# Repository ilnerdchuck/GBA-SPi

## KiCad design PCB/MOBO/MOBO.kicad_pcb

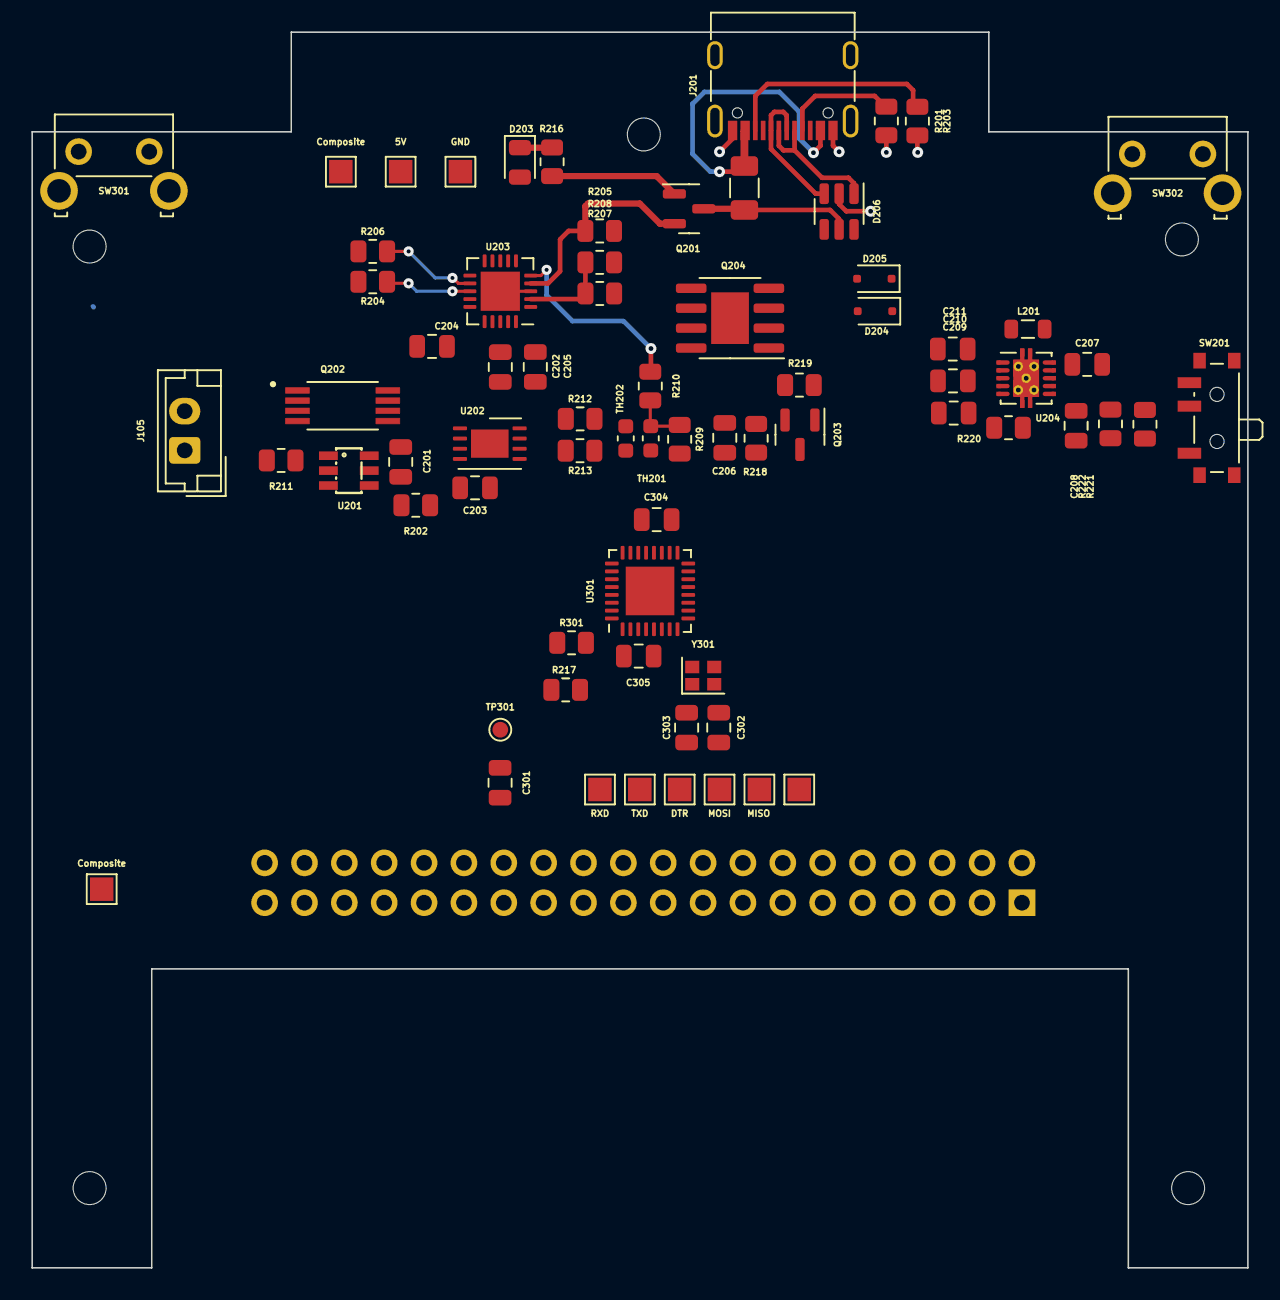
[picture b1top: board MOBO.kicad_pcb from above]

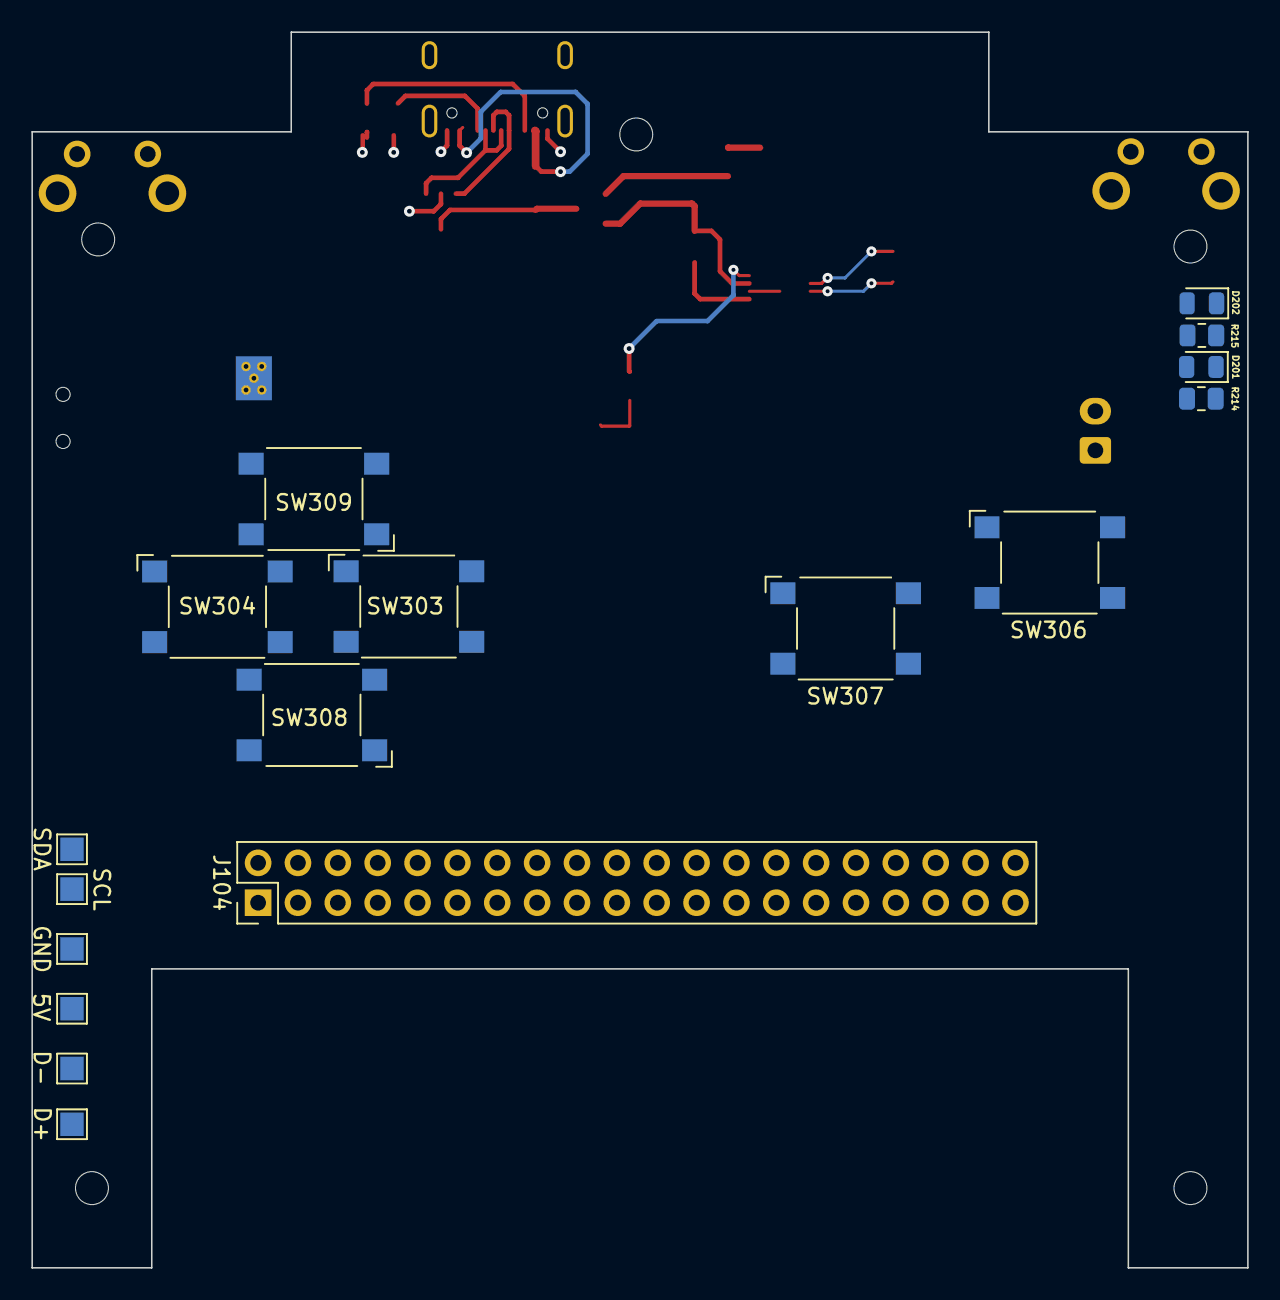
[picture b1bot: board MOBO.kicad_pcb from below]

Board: 2 copper layers, 77.5 x 78.7 mm, 93 parts (21 on the bottom side), 61 nets.

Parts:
5V: COMP_5V; TestPoint_Pad_1.5x1.5mm
5V#2: RPi_Ts5V; TestPoint_Pad_1.5x1.5mm
C201, C301: 100nF; C_0805_2012Metric
C202: 10uF; C_0805_2012Metric
C203: 1uF; C_0805_2012Metric
C204, C205, C304, C305: 4.7uF; C_0805_2012Metric
C206, C208: 10nF; C_0805_2012Metric
C207, C209, C210, C211: 22uF; C_0805_2012Metric
C302, C303: 22pF; C_0805_2012Metric
Composite: RPi_TV; TestPoint_Pad_1.5x1.5mm
Composite#2: COMP_OUT; TestPoint_Pad_1.5x1.5mm
D201: FULL; LED_0805_2012Metric
D202: CHRG; LED_0805_2012Metric
D203: PW_GOOD; LED_0805_2012Metric
D204, D205: BAT54J; D_SOD-323F
D206: USBLC6-2SC6; SOT-23-6
D+: RPi_D+; TestPoint_Pad_1.5x1.5mm
D-: RPi_D-; TestPoint_Pad_1.5x1.5mm
DTR: DTR; TestPoint_Pad_1.5x1.5mm
F201: 2A; Fuse_1206_3216Metric
GND: COMP_GND; TestPoint_Pad_1.5x1.5mm
GND#2: RPi_TsGND; TestPoint_Pad_1.5x1.5mm
H101, H102, H103, H104, H105: MountingHole; MountingHole_2.1mm
J104: RPi_GPio; PinHeader_2x20_P2.54mm_Vertical
J105: JST_02; JST_EH_B2B-EH-A_1x02_P2.50mm_Vertical
J201: MAIN-USBC-OTG/PWR; USB_C_Receptacle_G-Switch_GT-USB-7010ASV
L201: 1uH; L_0805_2012Metric
MISO: MISO; TestPoint_Pad_1.5x1.5mm
MOSI: MOSI; TestPoint_Pad_1.5x1.5mm
Q201: AO3401A; SOT-23
Q202: FS8205A; SOP65P640X120-8N
Q203: IRLML6344; SOT-23
Q204: Si4435DDY; SOIC-8-1EP_3.9x4.9mm_P1.27mm_EP2.41x3.3mm
R201, R203: 5.1K; R_0805_2012Metric
R202, R213, R217: 100; R_0805_2012Metric
R204: 1K; R_0805_2012Metric
R205: 10K; R_0805_2012Metric
R206: 30K; R_0805_2012Metric
R207: 310k; R_0805_2012Metric
R208: 110k; R_0805_2012Metric
R209: 69.8k; R_0805_2012Metric
R210: 1.54k; R_0805_2012Metric
R211: 1k; R_0805_2012Metric
R212, R301: 10k; R_0805_2012Metric
R214, R215, R216: 470; R_0805_2012Metric
R218, R220: 1M; R_0805_2012Metric
R219, R222: 100k; R_0805_2012Metric
R221: 402k; R_0805_2012Metric
RXD: RXD; TestPoint_Pad_1.5x1.5mm
SCL: RPi_SCL0; TestPoint_Pad_1.5x1.5mm
SDA: RPi_SDA0; TestPoint_Pad_1.5x1.5mm
SK: SCK; TestPoint_Pad_1.5x1.5mm
SW201: PCM12SMTR; SW_SPDT_PCM12
SW301: RS Button; SW_SPST_Omron_B3F-315x_Angled
SW302: LS Button; SW_SPST_Omron_B3F-315x_Angled
SW303: DPAD Right; SW_SPST_Omron_B3FS-100xP
SW304: DPAD Left; SW_SPST_Omron_B3FS-100xP
SW306: B Button; SW_SPST_Omron_B3FS-100xP
SW307: A Button; SW_SPST_Omron_B3FS-100xP
SW308: DPAD Down; SW_SPST_Omron_B3FS-100xP
SW309: DPAD Up; SW_SPST_Omron_B3FS-100xP
TH201, TH202: NCU18XH103F6SRB; C_0603_1608Metric
TP301: RES; TestPoint_Pad_D1.0mm
TXD: TXD; TestPoint_Pad_1.5x1.5mm
U201: DW01A; SOT23-6
U202: LC709203FQH-01TWG; WDFN-8-1EP_4x3mm_P0.65mm_EP2.4x1.8mm
U203: MCP73871-1AA; QFN-20-1EP_4x4mm_P0.5mm_EP2.5x2.5mm
U204: TPS61230DRC; Texas_S-PVSON-N10_ThermalVias
U301: ATmega328PB-M; QFN-32-1EP_5x5mm_P0.5mm_EP3.1x3.1mm
Y301: YABM11-16.000MHZ-12-B1U-T; Crystal_SMD_2016-4Pin_2.0x1.6mm

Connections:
+3V8: C207.1, C304.1, C305.1, L201.1, Q204.1 (S), Q204.2 (S), Q204.3 (S), R301.2, U204.9 (EN), U204.10 (VIN), U301.4 (VCC), U301.18 (AVCC)
+5V: 5V.1, 5V#2.1, C209.1, C210.1, C211.1, R220.2, R221.2, U204.3 (VOUT), U204.4 (VOUT)
+5VA: D206.5 (VP), F201.2, Q201.3 (D)
+5VD: C202.1, Q201.2 (S), R205.1, R207.1, U203.4 (PROG2), U203.17 (CE), U203.18 (IN), U203.19 (IN)
/Power & Charging/Charger 3V8 out: C205.1, C206.1, Q204.5 (D), Q204.6 (D), Q204.7 (D), Q204.8 (D), R218.1, U203.1 (OUT), U203.20 (OUT)
/Power & Charging/D+_IN: D206.1 (L1), J201.A7 (D-), J201.B7 (D-)
/Power & Charging/D-_IN: D206.3 (L2), J201.A6 (D+), J201.B6 (D+)
/Power & Charging/Latch Enable: C206.2, D205.2 (A), Q203.3 (D), Q204.4 (G), R218.2
/Power & Charging/Latch Hold: D204.2 (A), Q203.1 (G), R217.2, R219.1
/Power & Charging/PG: D203.2 (A), U203.6 (~PG)
/Power & Charging/STAT1: D202.2 (A), U203.8 (STAT1/~LBO)
/Power & Charging/STAT2: D201.2 (A), U203.7 (STAT2)
/Power & Charging/VPCC: R207.2, R208.1, U203.2 (VPCC)
ATMEGA_LATCH_S: R217.1, U301.1 (PD3)
BAT+: C203.1, C204.1, J105.1, R202.1, U202.3 (V_{DD}), U203.14 (V_{BAT}), U203.15 (V_{BAT}), U203.16 (V_{BAT_SENSE})
BAT-: C201.2, J105.2, Q202.2, Q202.3, U201.6 (GND)
BTN_A: SW307.1, U301.12 (PB0)
BTN_B: SW306.1, U301.13 (PB1)
BTN_DWN: SW308.1, U301.24 (PC1)
BTN_LEFT: SW304.1, U301.25 (PC2)
BTN_LS: SW302.1, U301.14 (PB2)
BTN_RIGHT: SW303.1, U301.26 (PC3)
BTN_RS: SW301.1, U301.32 (PD2)
BTN_UP: SW309.1, U301.23 (PC0)
CC1: J201.A5 (CC1), R201.1
CC2: J201.B5 (CC2), R203.1
COMPOSITE: Composite.1, Composite#2.1
D+: D206.4 (L2), D+.1
D-: D206.6 (L1), D-.1
GND: C202.2, C203.2, C204.2, C205.2, C207.2, C208.2, C209.2, C210.2, C211.2, C302.2, C303.1, C304.2, C305.2, D206.2 (VN), GND.1, GND#2.1, J201.A1 (GND), J201.A12 (GND), J201.B1 (GND), J201.B12 (GND), J201.S1 (SHIELD), Q201.1 (G), Q202.6, Q202.7, Q203.2 (S), R201.2, R203.2, R204.2, R205.2, R206.2, R208.2, R209.2, R211.2, R214.2, R215.2, R216.2, R219.2, R222.1, SW201.1, SW301.2, SW302.2, SW303.2, SW304.2, SW306.2, SW307.2, SW308.2, SW309.2, TH201.2, TH202.2, U202.1 (TEST), U202.2 (V_{SS}), U203.3 (SEL), U203.9 (~TE), U203.10 (V_{SS}), U203.11 (V_{SS}), U203.21 (V_{SS}), U204.11 (GND), U301.5 (GND), U301.21 (GND), U301.33 (GND)
MISO: MISO.1, U301.16 (PB4)
MOSI: MOSI.1, U301.15 (PB3)
unnamed: C301.2, DTR.1
unnamed: D201.1 (K), R214.1
unnamed: D202.1 (K), R215.1
unnamed: D203.1 (K), R216.1
unnamed: D204.1 (K), D205.1 (K), SW201.2
unnamed: L201.2, U204.1 (SW), U204.2 (SW)
unnamed: R209.1, R210.2, TH201.1
unnamed: R211.1, U201.2 (CS)
unnamed: Q202.5, U201.3 (OC)
unnamed: Q202.4, U201.1 (OD)
unnamed: C201.1, R202.2, U201.5 (VCC)
unnamed: R213.2, U202.6 (T_{SENSE})
unnamed: R212.1, U202.5 (T_{SW})
unnamed: R221.1, R222.2, U204.7 (FB)
unnamed: R220.1, U204.5 (PG)
unnamed: C208.1, U204.6 (SS)
unnamed: C302.1, U301.7 (XTAL1/PB6), Y301.1
unnamed: C303.2, U301.8 (XTAL2/PB7), Y301.2
PROG1: R204.1, U203.13 (PROG1)
PROG3: R206.1, U203.12 (PROG3)
RESET: C301.1, R301.1, TP301.1, U301.29 (~RESET/PC6)
RXD: RXD.1, U301.30 (PD0)
SCK: SK.1, U301.17 (PB5)
SCL: SCL.1, U202.8 (SCL), U301.28 (PC5)
SDA: SDA.1, U202.7 (SDA), U301.27 (PC4)
THERM: R210.1, U203.5 (THERM)
THERM2: R212.2, R213.1, TH202.1
TXD: TXD.1, U301.31 (PD1)
VBUS: F201.1, J201.A4 (VBUS), J201.A9 (VBUS), J201.B4 (VBUS), J201.B9 (VBUS)

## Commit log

2023-12-30 fixed 5v RPi power rail to not bypass the internal RPi fuse
2023-12-30 added parts links in BOM
2023-12-30 fixed testpoint footprint
2023-12-30 fixed buttons footprint
2023-12-30 added ATMega decoupling capacitors
2023-12-30 schematic cleanup
2023-12-31 added mounting holes
2024-01-01 fixed rpi gpio footprint
2024-01-01 switched to a pad for atmega reset
2024-01-04 fixed schematic net names
2024-01-04 Placed footprints
2024-02-24 Started pcb traces
2024-02-25 Added Driver packet handling
2024-06-03 reviewed and staged some schematic changes to be done
2024-06-03 removed battery protection and gauge circuit
2024-06-21 replaced latching circuit PMOS
2024-11-29 fix: battery charging protection module
